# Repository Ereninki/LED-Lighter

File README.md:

# LED-Lighter
My actuall first hardware project

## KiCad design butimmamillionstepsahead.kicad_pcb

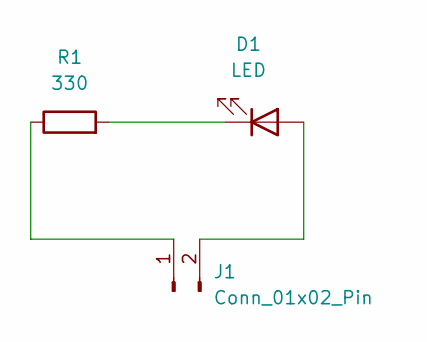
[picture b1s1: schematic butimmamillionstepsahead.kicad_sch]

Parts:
D1: LED; LED_D8.0mm
J1: Conn_01x02_Pin; PinHeader_1x02_P2.00mm_Vertical
R1: 330; R_Axial_DIN0207_L6.3mm_D2.5mm_P7.62mm_Horizontal

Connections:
unnamed: D1.2 (A), J1.2
unnamed: D1.1 (K), R1.2
unnamed: J1.1, R1.1

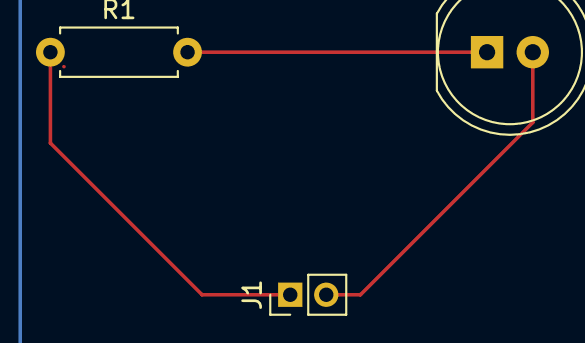
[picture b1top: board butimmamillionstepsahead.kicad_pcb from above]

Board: 2 copper layers, 3 parts (0 on the bottom side), 3 nets.

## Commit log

2026-06-10 added .gitignore
2026-06-10 cleaned the cache
2026-06-10 added assets
